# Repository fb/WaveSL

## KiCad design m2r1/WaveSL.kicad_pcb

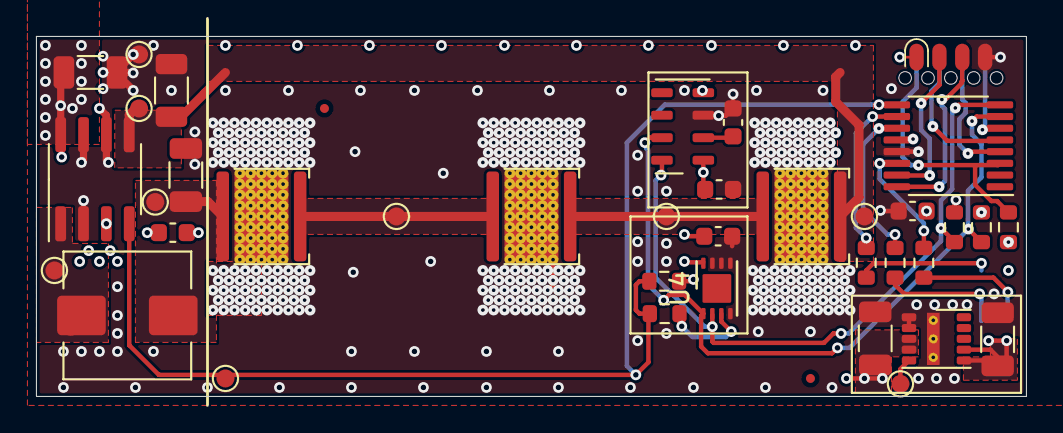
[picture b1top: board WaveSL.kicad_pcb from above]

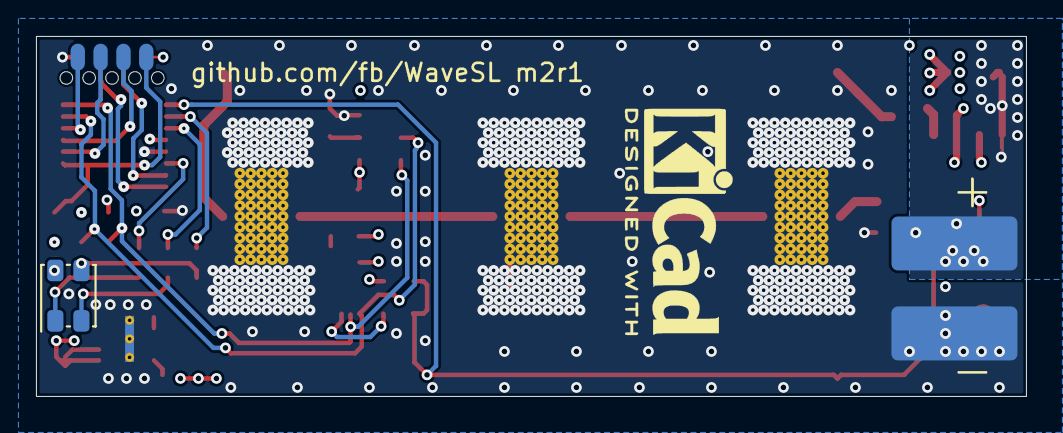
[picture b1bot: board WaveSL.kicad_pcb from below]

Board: 4 copper layers, 55.0 x 20.0 mm, 41 parts (2 on the bottom side), 26 nets.

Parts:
C1, C5: 10u; C_1206_3216Metric
C2: 1u; C_0603_1608Metric
C3: 2.2u; C_1206_3216Metric
C4: 33u; C_1206_3216Metric
C6, C7, C8, C9: 100n; C_0603_1608Metric
D1, D2, D3: XMLBWT-00-0000-0000T5051; LED_Cree-XLAMP-XM-L
D4: AAA3528SEEZGKQBKS; LED_Kingbright_AAA3528SEEZGKQBKS
FID1, FID2: Fiducial; Fiducial_0.5mm_Mask1mm
J1: Screw_Terminal_01x02; SolderWire-foo
J2: SOICBite; Connector_SOICbite
L1: 3.3u; L_Wuerth_HCI-7030
R1: 0R05; R_1206_3216Metric
R2: 1k5; R_0603_1608Metric
R3, R4: 270R; R_0603_1608Metric
R5, R6, R7, R8: 10k; R_0603_1608Metric
R9: 0R; R_0603_1608Metric
TP1, TP2, TP3, TP4, TP5, TP6, TP7, TP13, TP16: TestPoint; TestPoint_Pad_D1.0mm
U1: LED2000DR; SOIC-8_3.9x4.9mm_P1.27mm
U2: LMZM23600V3SILR; Texas_SIL0010A_MicroSiP-10-1EP_3.8x3mm_P0.6mm_EP0.7x2.9mm_T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
U3: MPL3115A2; NXP_LGA-8_3x5mm_P1.25mm_H1.1mm
U4: LM75BTP; HWSON-8-1EP_3x2mm_P0.5mm_EP1.6x1.6mm
U5: LPC812M001JDH16; TSSOP-16_4.4x5mm_P0.65mm

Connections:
+3V3: C4.1, C7.2, C8.1, C9.1, D4.2, J2.1, R5.2, R6.2, R7.2, R8.2, U2.6, U2.7, U3.1, U3.4, U4.8, U5.12
/GPIO: J2.6, U5.4
/LED+: C3.1, D1.2, L1.2, TP1.1
/LED-: D3.1, R1.1, TP5.1, TP16.1, U1.5
/LED_B: R4.1, U5.10
/LED_G: R3.1, U5.11
/LED_R: R2.1, U5.14
/RXD: J2.2, U5.15
/SCK: R6.1, U3.8, U4.2, U5.8
/SDA: R7.1, U3.7, U4.1, U5.7
/SWCLK: J2.7, U5.5
/SWDIO: J2.5, U5.6
/TXD: J2.3, U5.16
/~RESET: J2.8, R8.1, U5.3
GND: C1.2, C2.2, C3.2, C4.2, C5.2, C6.1, C7.1, C8.2, C9.2, D1.3, D2.3, D3.3, J1.2, J2.4, R1.2, TP7.1, U1.2, U1.6, U1.7, U2.1, U2.2, U2.11, U3.3, U4.4, U4.5, U4.6, U4.7, U5.13
unnamed: C6.2, U3.2
unnamed: D1.1, D2.2, TP2.1
unnamed: D2.1, D3.2, TP6.1
unnamed: D4.1, R2.2
unnamed: D4.3, R4.2
unnamed: D4.4, R3.2
unnamed: L1.1, TP3.1, U1.1
unnamed: R9.2, U4.3
unnamed: TP13.1, U2.5
PWM: R5.1, R9.1, TP4.1, U1.4, U5.9
VCC: C1.1, C2.1, C5.1, J1.1, U1.3, U1.8, U2.3, U2.4

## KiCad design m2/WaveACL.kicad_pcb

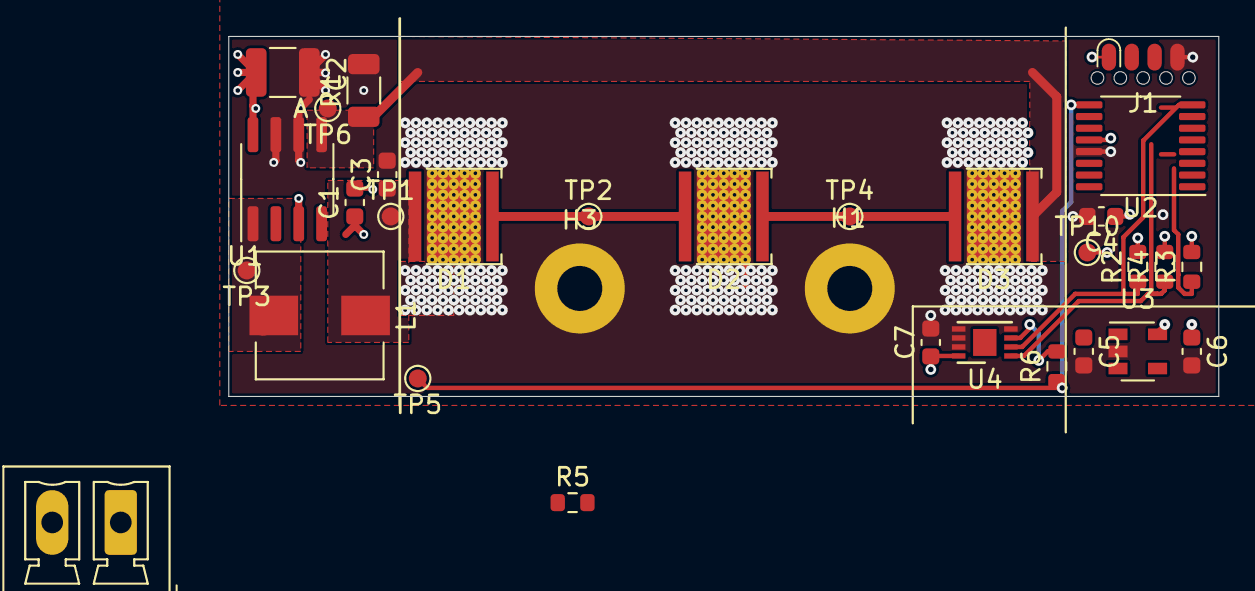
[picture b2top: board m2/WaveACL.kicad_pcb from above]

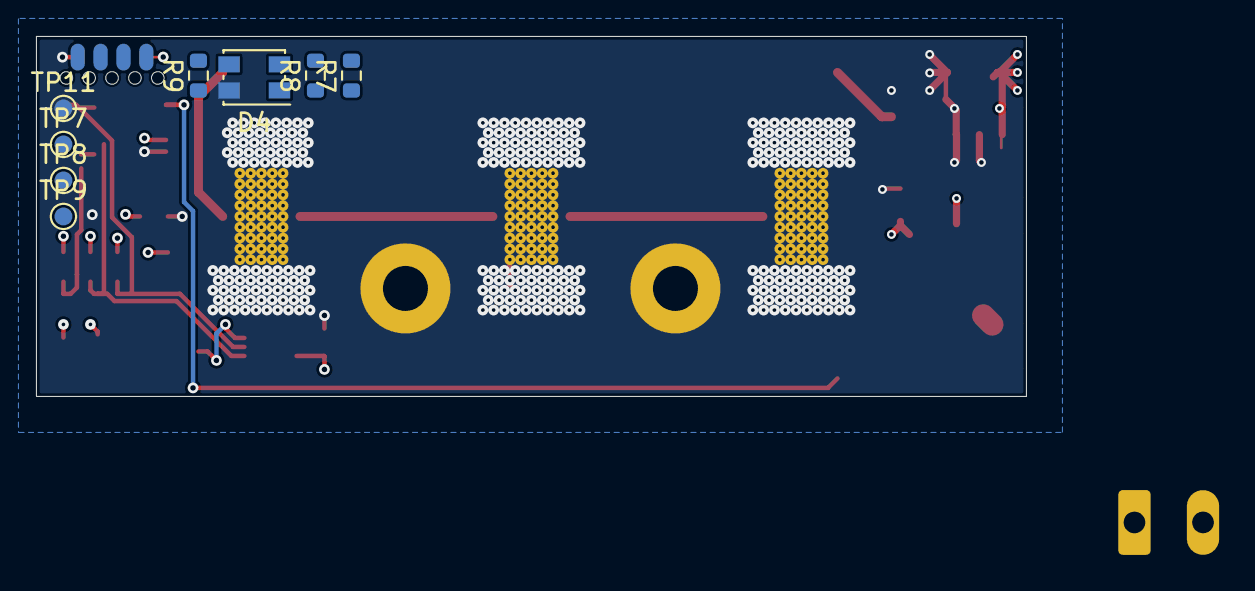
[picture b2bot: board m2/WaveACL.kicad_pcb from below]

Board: 4 copper layers, 55.0 x 20.0 mm, 40 parts (8 on the bottom side), 24 nets.

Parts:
C1: 1u; C_0603_1608Metric
C2: 10u; C_1210_3225Metric
C3: 2.2u; C_0603_1608Metric
C4, C5, C6, C7: 100n; C_0603_1608Metric
D1, D2, D3: LED; LED_Cree-XLAMP-XM-L
D4: LED_RABG; LED_Kingbright_AAA3528ESGCT
H1: MountingHole; MountingHole_2.5mm_Pad
H3: MountingHole_Pad; MountingHole_2.5mm_Pad
J1: SOICBite; Connector_SOICbite
J4: Screw_Terminal_01x02; PhoenixContact_MCV_1,5_2-G-3.81_1x02_P3.81mm_Vertical
L1: 2.2u; L_Wuerth_HCI-7030
R1: R; R_1206_3216Metric
R2, R3, R4, R5, R6, R7, R8, R9: R; R_0603_1608Metric
TP1, TP2, TP3, TP4, TP5, TP6, TP7, TP8, TP9, TP10, TP11: TestPoint; TestPoint_Pad_D1.0mm
U1: LED2000; SOIC-8_3.9x4.9mm_P1.27mm
U2: LPC812M001JDH16; TSSOP-16_4.4x5mm_P0.65mm
U3: TPS7A0533PDBV; SOT-23-5
U4: LM75B; DFN-8-1EP_3x2mm_P0.5mm_EP1.3x1.5mm

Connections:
+3V3: C4.1, C6.1, C7.1, J1.1, R2.2, R3.2, R4.2, R5.2, TP10.1, U2.12, U3.5, U4.8
/GPIO: J1.6, U2.4
/LED+: C3.1, D1.2, L1.2, TP1.1
/LED-: D3.1, R1.1, TP6.1, U1.5
/LED_B: R9.1, U2.10
/LED_G: R8.1, U2.11
/LED_R: R7.1, U2.14
/RXD: J1.2, U2.15
/SCK: R2.1, U2.8, U4.2
/SDA: R4.1, U2.7, U4.1
/SWCLK: J1.7, U2.5
/SWDIO: J1.5, U2.6
/TXD: J1.3, U2.16
/~RESET: J1.8, R3.1, U2.3
GND: C1.2, C2.2, C3.2, C4.2, C5.2, C6.2, C7.2, D1.3, D2.3, D3.3, D4.2, H1.1, H3.1, J1.4, R1.2, TP11.1, U1.2, U1.6, U1.7, U2.13, U3.2, U4.4, U4.5, U4.6, U4.7
unnamed: D1.1, D2.2, TP2.1
unnamed: D2.1, D3.2, TP4.1
unnamed: D4.1, R7.2, TP7.1
unnamed: D4.3, R9.2, TP9.1
unnamed: D4.4, R8.2, TP8.1
unnamed: L1.1, TP3.1, U1.1
unnamed: R6.2, U4.3
PWM: R5.1, R6.1, TP5.1, U1.4, U2.9
VCC: C1.1, C2.1, C5.1, U1.3, U1.8, U3.1, U3.3

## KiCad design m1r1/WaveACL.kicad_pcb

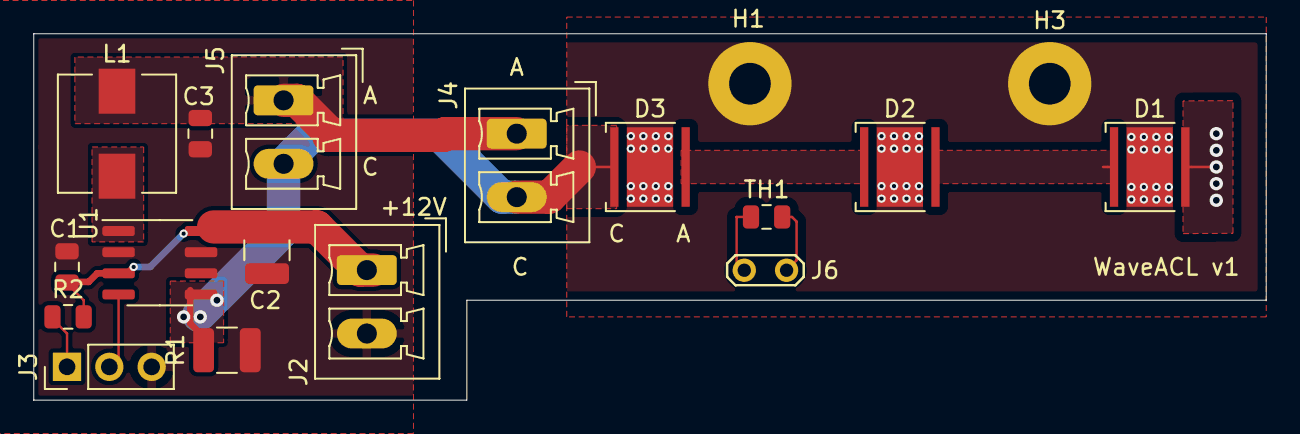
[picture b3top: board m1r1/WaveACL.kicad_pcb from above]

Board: 2 copper layers, 74.0 x 22.0 mm, 18 parts (0 on the bottom side), 12 nets.

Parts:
C1: 100n; R_0805_2012Metric
C2: 10u; C_1210_3225Metric
C3: 2.2u; C_0805_2012Metric
D1, D2, D3: LED; LED_Cree-XHP50_6V
H1: MountingHole; MountingHole_2.5mm_Pad
H3: MountingHole_Pad; MountingHole_2.5mm_Pad
J2, J4, J5: Conn_01x02; PhoenixContact_MCV_1,5_2-G-3.81_1x02_P3.81mm_Vertical
J3: Conn_01x03; PinHeader_1x03_P2.54mm_Vertical
J6: Conn_01x02; TestPoint_2Pads_Pitch2.54mm_Drill0.8mm
L1: 2.2u; L_Wuerth_HCI-7030
R1: R; R_1210_3225Metric
R2: 4K7; R_0805_2012Metric
TH1: Thermistor_NTC; R_0805_2012Metric
U1: LED2000; SOIC-8_3.9x4.9mm_P1.27mm

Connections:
/HS1: D1.3, D2.3, D3.3, H1.1, H3.1
/LED+: C3.1, D1.2, J4.1, J5.1, L1.2
/LED-: D3.1, J4.2, J5.2, R1.1, U1.5
GND: C1.2, C2.2, C3.2, J2.2, J3.3, R1.2, U1.2, U1.6, U1.7
unnamed: D1.1, D2.2
unnamed: D2.1, D3.2
unnamed: J3.1, R2.1
unnamed: J6.1, TH1.2
unnamed: J6.2, TH1.1
unnamed: L1.1, U1.1
PWM: J3.2, U1.4
VCC: C1.1, C2.1, J2.1, R2.2, U1.3, U1.8

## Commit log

2021-03-07 init
2021-03-07 Mark1 Rev1
2021-03-07 WIP Mark2
2021-03-09 add fkl
2021-03-09 Mark2 updates
    - add I2C temp. sensor
    - add voltage regulator for uC
2021-03-09 add SOICByte Footprint
2021-03-13 update m2
2021-03-18 tidy up silkscreen layer
2021-03-21 updates
    - LMZM23600V3SIL for 3.3 V
    - AAA3528SEEZGKQBKS as status LED
    - pads for VIN
    - …
2021-03-22 update footprints and add U3 sensor
2021-03-22 finalize mk2 rev1
2021-03-26 fill in values
2021-03-26 cleanup F.Fab and add IBOM
2021-03-31 enhance for 3d export
